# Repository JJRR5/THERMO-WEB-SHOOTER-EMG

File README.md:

# THERMO-WEB-SHOOTER-EMG
Development proyect

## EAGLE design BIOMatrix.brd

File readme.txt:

Hello everybody!, this proyect is about develop a web shooter which is gonna be controlled by EMG signals and it is gonna work like a thermometer

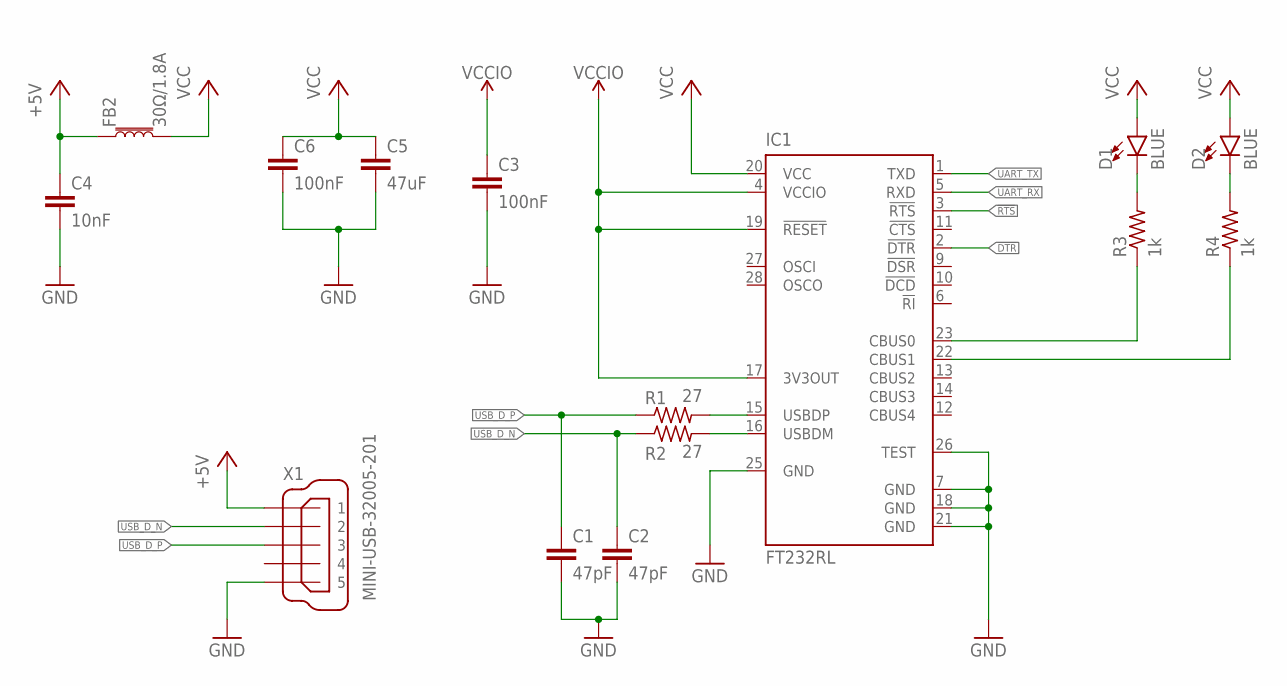
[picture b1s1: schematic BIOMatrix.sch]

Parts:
C1, C2: 47pF; C0603
C3, C6: 100nF; C0603
C4: 10nF; C0603
C5: 47uF; C0603
D1, D2: BLUE; LED-0603
FB2: 30Ω/1.8A; 0603
IC1: FT232RL; SSOP28
R1, R2: 27; R0603
R3, R4: 1k; R0603
X1: MINI-USB-32005-201; 32005-201

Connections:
!DTR: IC1.2 (!DTR)
!RTS: IC1.3 (!RTS)
+5V: C4.1, FB2.1, X1.1
GND: C1.2, C2.2, C3.2, C4.2, C5.2, C6.2, IC1.7 (GND), IC1.18 (GND), IC1.21 (GND), IC1.25 (GND), IC1.26 (TEST), X1.5
unnamed: IC1.15 (USBDP), R1.2
unnamed: D1.C, R3.2
unnamed: IC1.16 (USBDM), R2.2
unnamed: D2.C, R4.2
unnamed: IC1.23 (CBUS0), R3.1
unnamed: IC1.22 (CBUS1), R4.1
UART_RX: IC1.5 (RXD)
UART_TX: IC1.1 (TXD)
USB_D_N: C2.1, R2.1, X1.2
USB_D_P: C1.1, R1.1, X1.3
VCC: C5.1, C6.1, D1.A, D2.A, FB2.2, IC1.20 (VCC)
VCCIO: C3.1, IC1.4 (VCCIO), IC1.17 (3V3OUT), IC1.19 (!RESET)

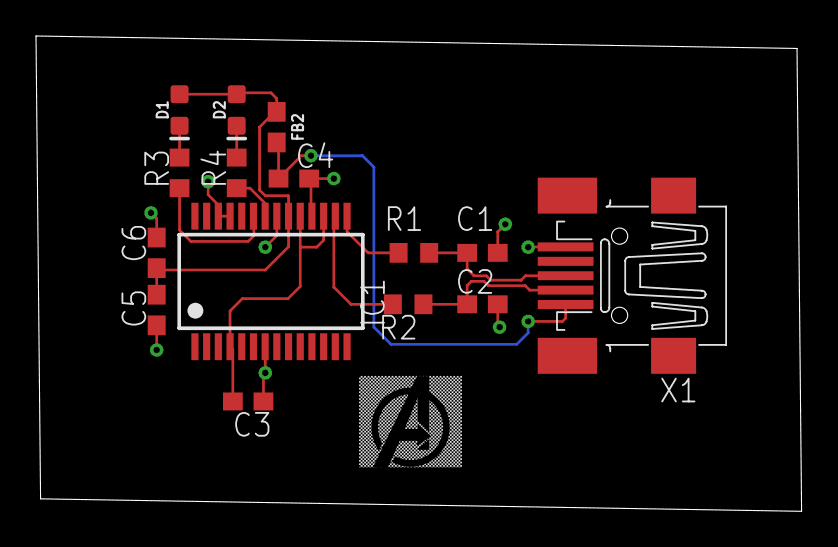
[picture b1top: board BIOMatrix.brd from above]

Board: 2 copper layers, 42.5 x 26.4 mm, 15 parts (0 on the bottom side), 12 nets.

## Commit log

2021-02-26 ADDED THE BLOCK DIAGRAM OF THE CIRCUIT
    Added a .JPG file
2021-02-28 Added the ESP-12F data sheet
2021-02-28 Added the Prototype 1.0 of the web shooter
2021-02-28 Added the Functioning Diagram
2021-03-01 ESP-12F Data Sheet
    Added the data sheet of the microcontroller
2021-03-02 ESP12F-Schematic and Board
    Added the two files of the ESP-12F
2022-01-02 IDEAS
2022-01-04 EMG circuit
2022-01-06 AD620 datasheet
2022-02-08 READ ME

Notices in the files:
parts and their libraries:
SparkFun-LED: Licensing: Creative Commons ShareAlike 4.0 International - https://creativecommons.org/licenses/by-sa/4.0
